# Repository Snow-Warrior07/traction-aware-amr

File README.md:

# Traction-aware warehouse rover

An entirely virtual control-engineering project: a differential-drive rover, linear PI/LQR and nonlinear tracking, traction estimation/supervision, ROS 2, a custom controller PCB, and live tests.

The plant models independent wheel/body velocity, motor current, payload and friction-limited contact. A noisy delayed pose sensor plus wheel encoders and IMU feeds the estimator. Simulator truth is used only for sensor generation and evaluation.

· [Phase results](docs/PHASE_RESULTS.md) · [Download KiCad project](https://snow-warrior07.github.io/traction-aware-amr/downloads/traction-aware-amr-kicad.zip) · [PDF report](https://snow-warrior07.github.io/traction-aware-amr/downloads/phase-report.pdf)

The demo includes four-controller recorded playback, supervisor-off overlays, filters across 540 measured scenarios, actual PCB/schematic views, ROS and Gazebo evidence, fault/timing tables, and a narrated video with captions. It runs entirely in the browser; physical hardware is unnecessary.

Local KiCad 10.0.6 checks: **zero ERC violations, zero DRC violations, zero unconnected items, and zero schematic/PCB parity issues**. The 29-component board has 29 connected signal/power nets plus 18 single-pad no-connect nets. Source, project libraries, Gerbers, drills, netlist, renders, and board STEP are included. On the development computer the editable project is also on the Desktop in `TractionAwareAMR-KiCad/traction_carrier.kicad_pro`.

All 540 routes completed. Low-traction integrated-slip reduction was 18.76% for LQR and 18.48% for nonlinear tracking; the 20% hypothesis was not met. Four recorded soft real-time runs had zero 20 ms compute misses. Five injected faults disabled the drive. The corrected Gazebo torque/contact test passed separately from the mathematical-plant study; saved evidence is in `results/gazebo_smoke.json`.

GitHub verification tests are manual at the user's request. Prior failed runs are retained. GitHub Pages publication runs independently; no green CI badge is used as an engineering claim.

## Preview the website

```bash
python -m http.server 8080 --bind 127.0.0.1 --directory site
```

Open `http://127.0.0.1:8080/`. The website uses static HTML/CSS/JavaScript and saved JSON data; no backend or account is needed. If Windows reserves this port, use `0` instead and open the assigned port printed by Python. Package downloads/assets using `python tools/package_delivery.py` after generating the report/video. See `requirements-demo.txt` for authoring dependencies.

## Run locally

Use Python 3.12 and a 64-bit C++ compiler. Linux is the simplest reproduction environment. The Windows development host used MATLAB R2024b's installed LCC64 with the same C-compatible C++ source because its MinGW installation is 32-bit. Windows runtime math functions are bound explicitly; Linux uses standard libm.

```bash
python -m venv .venv
source .venv/bin/activate
pip install -r requirements.txt
python -m pytest -q
python -m amr.experiments smoke
python -m amr.experiments matrix --workers 4
python -m amr.experiments live --variant D --seconds 16
python -m amr.experiments faults
```

On Windows, use `.venv\Scripts\python.exe` for the Python commands. The native library is compiled from `firmware/core.cpp` on first import. Generated measurements go into `results/`.

## Phases

1. Requirements and fixed experiment criteria: `docs/requirements.md`, `config/robot.yaml`, `experiments/scenarios.yaml`.
2. Plant/contact dynamics and warehouse model: `firmware/core.cpp`, `amr/simulation.py`, `tools/generate_world.py`.
3. Actual ROS graph, service, TF and bag replay: `ros_ws/`, `tools/ros_smoke.py`, `tools/gazebo_smoke.py`.
4. Linear wheel PI and trajectory LQR: `amr/control.py`, native control core, stability and tracking tests.
5. Nonlinear controller, sensor estimator and supervisor: matched A/B/C/D comparison.
6. Pico carrier PCB, RC circuit and virtual I/O: `tools/generate_pcb.py`, `hardware/spice/`, `amr/board.py`.
7. Regression, faults, live timing and standards mapping: tests, saved results, phase report.
8. GitHub verification and public release: Actions artifacts and static demonstration.

Each phase is reported from executed evidence in `docs/PHASE_RESULTS.md`. Website playback replays recorded measurements; it does not execute ROS or KiCad in the browser.

## Controller comparison

| Variant | Outer controller | Traction supervisor |
|---|---|---|
| A | LQR | Off |
| B | LQR | On |
| C | Nonlinear | Off |
| D | Nonlinear | On |

The full matrix contains 540 runs: four variants, three traction conditions, three payloads, three routes and five noise seeds. Acceleration/braking demands exercise traction while crossing a low-friction patch. Slip reduction is measured rather than assumed, and delivery-time/error/energy tradeoffs remain visible.

## ROS and PCB verification

The workflow runs Ubuntu 24.04, ROS 2 Jazzy/Gazebo Harmonic and KiCad 9/ngspice. ROS tests execute real DDS traffic, controller commands, transforms, a service call, and rosbag record/replay. Gazebo receives wheel effort through `ros_gz_bridge` and compares dry/low-friction contact. The four-controller matrix uses the inspectable mathematical plant; Gazebo contact tests are a separate validation, not identical numerical replicas.

The PCB is a custom Raspberry Pi Pico carrier for external motor drivers. Motor power does not flow through the logic carrier. External drivers provide 0.1 V/A centered current measurements and active-low faults; the PCB filters measurements and latches drive authorization independently of ROS. Part choices, pin assignments, routing and exports are inspectable. Selected RC circuits are modeled in ngspice; the whole assembled board, EMI and embedded timing are not physically validated.

Live runs are wall-clock-paced soft real-time tests on ordinary operating systems. Reports include compute deadline misses and wake-up lateness separately. They do not demonstrate hard real-time scheduling or safety certification.

See `docs/control-derivation.md`, `docs/standards.md`, and the measured `results/` files for model assumptions and scope.

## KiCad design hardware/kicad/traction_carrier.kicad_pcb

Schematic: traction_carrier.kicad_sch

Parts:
C1, C2: 1u; C_0805_2012Metric
C3, C4, C6, C7, C8: 100n; C_0805_2012Metric
C5: 10u; C_0805_2012Metric
J1: 5V power / 24V sense; PinHeader_1x03_P2.54mm_Vertical
J2: LEFT DRIVER; PinHeader_1x06_P2.54mm_Vertical
J3: RIGHT DRIVER; PinHeader_1x06_P2.54mm_Vertical
J4: LEFT ENCODER; PinHeader_1x04_P2.54mm_Vertical
J5: RIGHT ENCODER; PinHeader_1x04_P2.54mm_Vertical
J6: 3V3 IMU; PinHeader_1x04_P2.54mm_Vertical
J7: UART DEBUG; PinHeader_1x04_P2.54mm_Vertical
R1, R2: 1k; R_0805_2012Metric
R3: 100k; R_0805_2012Metric
R4, R7, R8, R9, R10: 10k; R_0805_2012Metric
R5, R6: 2.2k; R_0805_2012Metric
SW1: Manual drive reset; SW_PUSH_6mm_H4.3mm
U1: Raspberry Pi Pico RP2040; RaspberryPi_Pico_Common_THT
U2: 74HC08 AND gate; DIP-14_W7.62mm
U3: 74HC74 fault latch; DIP-14_W7.62mm

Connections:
/3V3: C4.1 (3V3), C6.1 (3V3), C7.1 (3V3), J4.1 (3V3), J5.1 (3V3), J6.1 (3V3), J7.1 (3V3), R5.1 (3V3), R6.1 (3V3), R9.1 (3V3), R10.1 (3V3), SW1.1 (3V3), U1.36 (3V3), U2.14 (3V3), U3.2 (3V3), U3.4 (3V3), U3.10 (3V3), U3.14 (3V3)
/5V: C5.1 (5V), J1.1 (5V), U1.39 (5V)
/ADC_BUS: C3.1 (ADC_BUS), R3.2 (ADC_BUS), R4.1 (ADC_BUS), U1.34 (ADC_BUS)
/ADC_CURRENT_L: C1.1 (ADC_CURRENT_L), R1.2 (ADC_CURRENT_L), U1.31 (ADC_CURRENT_L)
/ADC_CURRENT_R: C2.1 (ADC_CURRENT_R), R2.2 (ADC_CURRENT_R), U1.32 (ADC_CURRENT_R)
/ADC_VREF: C8.1 (ADC_VREF), U1.35 (ADC_VREF)
/ARMED: U2.5 (ARMED), U3.5 (ARMED)
/BUS_24V: J1.3 (BUS_24V), R3.1 (BUS_24V)
/DIR_L: J2.2 (DIR_L), U1.12 (DIR_L)
/DIR_R: J3.2 (DIR_R), U1.15 (DIR_R)
/DRIVE_ENABLE: J2.3 (DRIVE_ENABLE), J3.3 (DRIVE_ENABLE), U2.6 (DRIVE_ENABLE)
/ENC_L_A: J4.3 (ENC_L_A), U1.4 (ENC_L_A)
/ENC_L_B: J4.4 (ENC_L_B), U1.5 (ENC_L_B)
/ENC_R_A: J5.3 (ENC_R_A), U1.9 (ENC_R_A)
/ENC_R_B: J5.4 (ENC_R_B), U1.10 (ENC_R_B)
/FAULT_L_N: J2.6 (FAULT_L_N), R9.2 (FAULT_L_N), U2.1 (FAULT_L_N)
/FAULT_OK: U2.3 (FAULT_OK), U3.1 (FAULT_OK)
/FAULT_R_N: J3.6 (FAULT_R_N), R10.2 (FAULT_R_N), U2.2 (FAULT_R_N)
/GND: C1.2 (GND), C2.2 (GND), C3.2 (GND), C4.2 (GND), C5.2 (GND), C6.2 (GND), C7.2 (GND), C8.2 (GND), J1.2 (GND), J2.4 (GND), J3.4 (GND), J4.2 (GND), J5.2 (GND), J6.2 (GND), J7.2 (GND), R4.2 (GND), R7.2 (GND), R8.2 (GND), U1.3 (GND), U1.8 (GND), U1.13 (GND), U1.18 (GND), U1.23 (GND), U1.28 (GND), U1.33 (GND), U1.38 (GND), U2.7 (GND), U2.9 (GND), U2.10 (GND), U2.12 (GND), U2.13 (GND), U3.7 (GND), U3.11 (GND), U3.12 (GND), U3.13 (GND)
/ISENSE_L: J2.5 (ISENSE_L), R1.1 (ISENSE_L)
/ISENSE_R: J3.5 (ISENSE_R), R2.1 (ISENSE_R)
/MCU_ENABLE: R8.1 (MCU_ENABLE), U1.16 (MCU_ENABLE), U2.4 (MCU_ENABLE)
/PWM_L: J2.1 (PWM_L), U1.11 (PWM_L)
/PWM_R: J3.1 (PWM_R), U1.14 (PWM_R)
/RESET_CLOCK: R7.1 (RESET_CLOCK), SW1.2 (RESET_CLOCK), U3.3 (RESET_CLOCK)
/SCL: J6.4 (SCL), R6.2 (SCL), U1.7 (SCL)
/SDA: J6.3 (SDA), R5.2 (SDA), U1.6 (SDA)
/UART_RX: J7.4 (UART_RX), U1.2 (UART_RX)
/UART_TX: J7.3 (UART_TX), U1.1 (UART_TX)

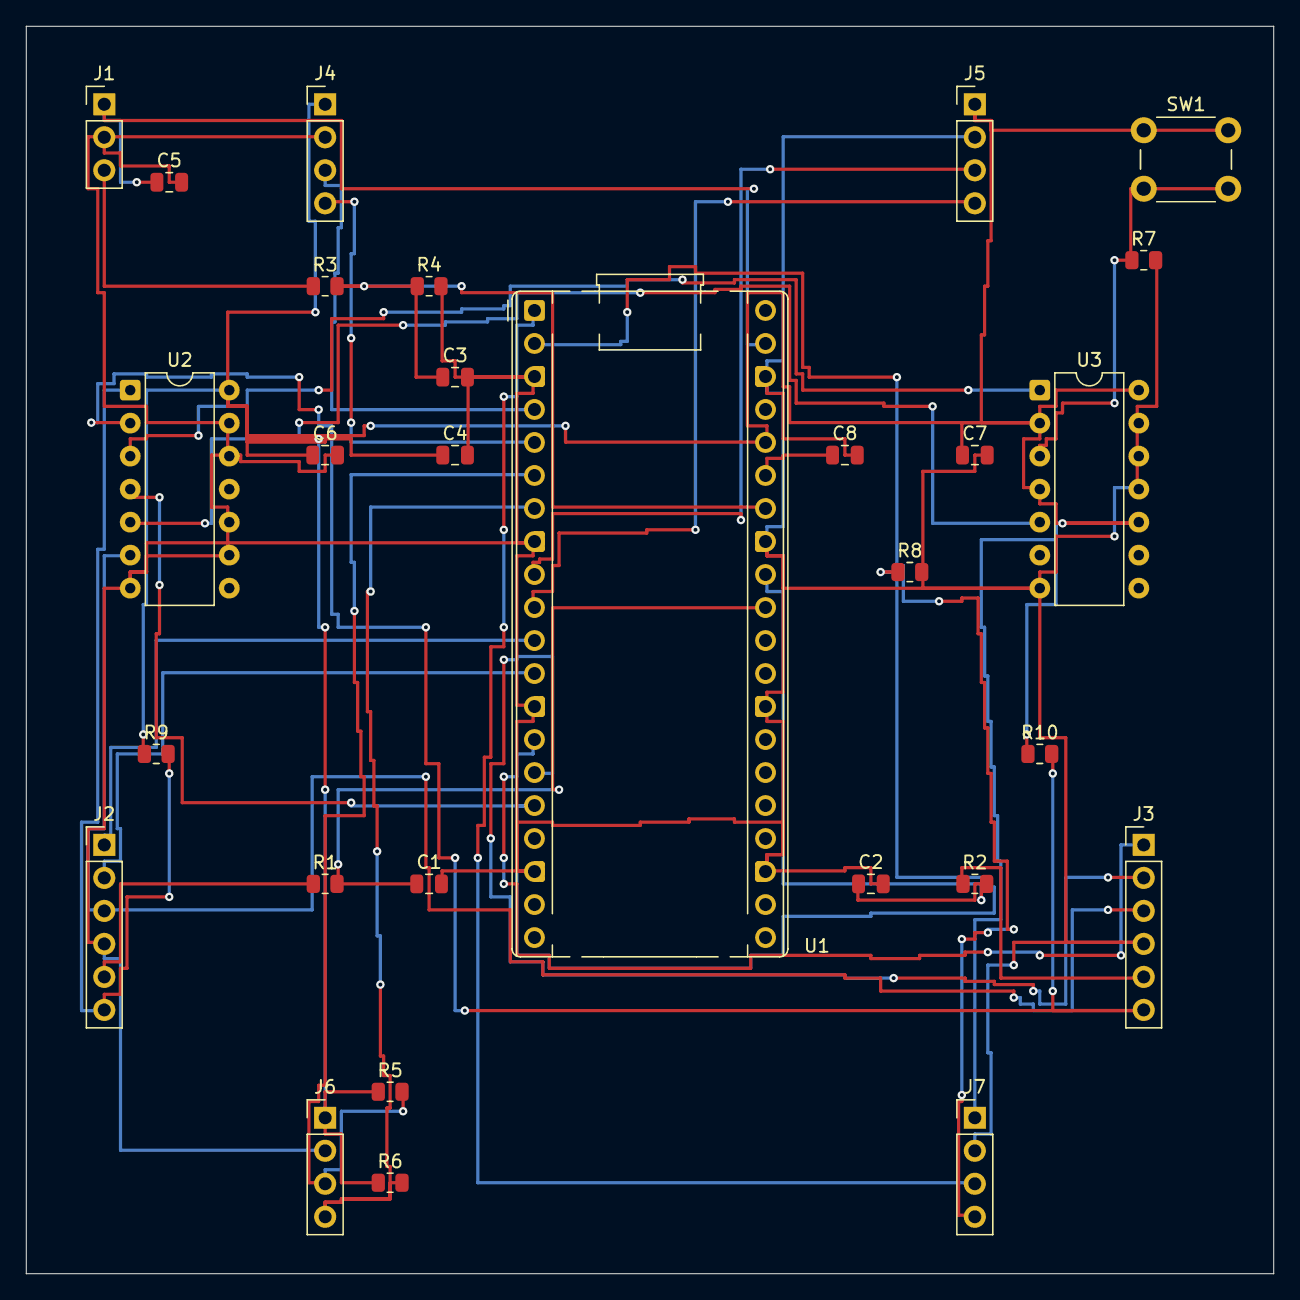
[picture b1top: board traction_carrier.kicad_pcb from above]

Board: 2 copper layers, 96.0 x 96.0 mm, 29 parts (0 on the bottom side), 29 nets.

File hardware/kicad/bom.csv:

Reference,Value,Footprint
U1,Raspberry Pi Pico RP2040,Module:RaspberryPi_Pico_Common_THT
U2,74HC08 AND gate,Package_DIP:DIP-14_W7.62mm
U3,74HC74 fault latch,Package_DIP:DIP-14_W7.62mm
J1,5V power / 24V sense,Connector_PinHeader_2.54mm:PinHeader_1x03_P2.54mm_Vertical
J2,LEFT DRIVER,Connector_PinHeader_2.54mm:PinHeader_1x06_P2.54mm_Vertical
J3,RIGHT DRIVER,Connector_PinHeader_2.54mm:PinHeader_1x06_P2.54mm_Vertical
J4,LEFT ENCODER,Connector_PinHeader_2.54mm:PinHeader_1x04_P2.54mm_Vertical
J5,RIGHT ENCODER,Connector_PinHeader_2.54mm:PinHeader_1x04_P2.54mm_Vertical
J6,3V3 IMU,Connector_PinHeader_2.54mm:PinHeader_1x04_P2.54mm_Vertical
J7,UART DEBUG,Connector_PinHeader_2.54mm:PinHeader_1x04_P2.54mm_Vertical
R1,1k,Resistor_SMD:R_0805_2012Metric
R2,1k,Resistor_SMD:R_0805_2012Metric
R3,100k,Resistor_SMD:R_0805_2012Metric
R4,10k,Resistor_SMD:R_0805_2012Metric
R5,2.2k,Resistor_SMD:R_0805_2012Metric
R6,2.2k,Resistor_SMD:R_0805_2012Metric
R7,10k,Resistor_SMD:R_0805_2012Metric
R8,10k,Resistor_SMD:R_0805_2012Metric
R9,10k,Resistor_SMD:R_0805_2012Metric
R10,10k,Resistor_SMD:R_0805_2012Metric
C1,1u,Capacitor_SMD:C_0805_2012Metric
C2,1u,Capacitor_SMD:C_0805_2012Metric
C3,100n,Capacitor_SMD:C_0805_2012Metric
C4,100n,Capacitor_SMD:C_0805_2012Metric
C5,10u,Capacitor_SMD:C_0805_2012Metric
C6,100n,Capacitor_SMD:C_0805_2012Metric
C7,100n,Capacitor_SMD:C_0805_2012Metric
C8,100n,Capacitor_SMD:C_0805_2012Metric
SW1,Manual drive reset,Button_Switch_THT:SW_PUSH_6mm_H4.3mm
